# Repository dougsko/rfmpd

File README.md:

# RFMP Daemon

RF Microblog Protocol (RFMP) v0.5 daemon for packet radio networks.

## Overview

RFMP is a decentralized, append-only microblogging protocol for AX.25 UI frame packet radio networks. This daemon provides:

- Full RFMP protocol (Protocol Buffers wire format)
- Scuttlebutt-style vector clock synchronization
- REST API and real-time WebSocket updates
- Integrated web UI on port 8080
- SQLite persistent storage (pure Go, no CGo)
- Automatic Direwolf integration via udev
- Single static binary (~15MB), cross-compiles to ARM
- Native packages: `.deb`, `.rpm`, `.apk`, plus tarball

## Prerequisites

- [Go 1.24+](https://go.dev/dl/) (build only)
- Linux (Debian-based) for deployment
- [Direwolf](https://github.com/wb2osz/direwolf) TNC
- Amateur radio license (for transmission)
- Supported radio interface: Digirig, Digirig Lite, or QRP Labs QMX

## Building

```bash
# Build for current platform (stripped, version info baked in)
make build

# Plain build for current platform
go build -o rfmpd .

# Cross-compile for Raspberry Pi (ARM64)
GOOS=linux GOARCH=arm64 go build -o rfmpd .

# Cross-compile for Raspberry Pi (ARMv7) / Orange Pi Zero
GOOS=linux GOARCH=arm GOARM=7 go build -o rfmpd .

# Build all native packages (.deb, .rpm, .apk) for arm64 + amd64 (requires Docker)
make dist
```

`make build` uses `-ldflags "-s -w -X main.version=…"` to strip debug symbols
(reducing binary size ~30%) and embed the version string from the Makefile.

No CGo is required — the SQLite driver (`modernc.org/sqlite`) is pure Go, so cross-compilation works without a C toolchain.

## Running Tests

```bash
# Run unit tests
go test ./...

# Run protocol simulation (end-to-end)
go build -o rfmpd . && go build -o rf-sim ./cmd/rf-sim/
./rf-sim                        # All scenarios, unlimited speed
./rf-sim --baud 1200            # Simulate 1200 baud VHF channel
./rf-sim --baud 300             # Simulate 300 baud HF channel
./rf-sim --verbose              # Show broker frame traffic
./rf-sim --continuous           # Continuous churn testing
```

The simulation spawns multiple rfmpd nodes connected through an in-process
KISS broker, then verifies message delivery under various conditions:
network partitions, node crashes, late joiners, and fragmentation.

## Quick Start

```bash
# Build for current platform
make build

# Run in offline mode (no Direwolf needed)
./rfmpd -c config.yaml.example

# Run with verbose logging
./rfmpd -c config.yaml.example -v

# Open the web UI
open http://localhost:8080
```

## Installation (Linux)

Install from a native package — the `.deb`, `.rpm`, and `.apk` packages bundle
the binary, default config, systemd/OpenRC unit files, Direwolf configs, and
udev rules. Build them with `make dist` (requires Docker):

```bash
make dist             # builds .deb, .rpm, .apk, and tarballs in ./dist/

# Debian/Ubuntu/Raspberry Pi OS
sudo apt install ./dist/rfmpd_*_arm64.deb

# Fedora/RHEL
sudo dnf install ./dist/rfmpd-*.aarch64.rpm

# Alpine
sudo apk add --allow-untrusted ./dist/rfmpd-*-aarch64.apk
```

After install, set your callsign and start the service:

```bash
sudo nano /etc/rfmpd/config.yaml                       # set callsign
sudo nano /etc/rfmpd/direwolf/direwolf-digirig.conf    # set MYCALL to match
sudo systemctl enable --now rfmpd
```

Direwolf starts automatically when a supported radio interface is plugged in
via USB. For systems without package support, see
[packaging/INSTALL.md](packaging/INSTALL.md) for the manual tarball flow.
See [DEPLOYMENT.md](DEPLOYMENT.md) for full details on the hardware lifecycle.

## Uninstalling

```bash
# Debian/Ubuntu — keep config and data
sudo apt remove rfmpd
# Debian/Ubuntu — remove everything including config
sudo apt purge rfmpd

# Fedora/RHEL
sudo dnf remove rfmpd

# Alpine
sudo apk del rfmpd
```

## Supported Hardware

| Interface | Band | Baud | PTT | USB ID |
|-----------|------|------|-----|--------|
| Digirig | VHF | 1200 | Serial RTS | `10c4:ea60` |
| Digirig Lite | VHF | 1200 | CM108 GPIO | `0d8c:0012` (hidraw) |
| QMX | HF | 300 | Hamlib CAT | `0483:a34c` |

The packages install udev rules that auto-detect these devices and start Direwolf with the correct configuration.

## Configuration

Config file: `/etc/rfmpd/config.yaml` (installed) or `./config.yaml` (dev)

```yaml
node:
  callsign: "N0CALL"    # Your callsign (REQUIRED)
  ssid: 0               # SSID 0-15

network:
  direwolf_host: "127.0.0.1"
  direwolf_port: 8001
  offline_mode: false    # true for testing without radio

sync:
  sync_interval: 60     # SVEC broadcast interval (seconds)

storage:
  database_path: "/var/lib/rfmpd/messages.db"

api:
  host: "0.0.0.0"
  port: 8080
  cors_origins:
    - "http://localhost:8080"
```

## API

The daemon serves a REST API on port 8080 (configurable):

| Endpoint | Method | Description |
|----------|--------|-------------|
| `/` | GET | Web UI |
| `/health` | GET | Health check |
| `/messages` | GET | List messages (filterable) |
| `/messages/{id}` | GET | Get specific message |
| `/messages` | POST | Send a message |
| `/channels` | GET | List active channels |
| `/nodes` | GET | List seen nodes |
| `/status` | GET | Daemon status and vector clock |
| `/config/callsign` | GET/POST | Get or set callsign |
| `/stream` | WS | Real-time WebSocket updates |

```bash
# Send a message
curl -X POST http://localhost:8080/messages \
  -H "Content-Type: application/json" \
  -d '{"channel": "general", "body": "Hello RFMP!"}'

# Get recent messages
curl http://localhost:8080/messages?channel=general&limit=10

# Check status
curl http://localhost:8080/status
```

See [openapi.yaml](openapi.yaml) for the full API specification.

## Protocol

RFMP v0.4 uses Protocol Buffers for the RF wire format:

- **MSG** — Message with per-node monotonic sequence number, epoch timestamp, binary ID
- **FRAG** — Fragment for messages exceeding threshold (raw protobuf bytes, no base64)
- **SVEC** — Vector clock broadcast for scuttlebutt synchronization (native map type)

Protobuf encoding saves 30-50% airtime versus the previous text format. Synchronization uses per-node sequence numbers. Nodes broadcast their vector clock via SVEC frames; on receiving a remote SVEC, the local node pushes any messages the remote is missing.

See [docs/PROTOCOL.md](docs/PROTOCOL.md) for the complete protocol specification and [test_vectors.json](test_vectors.json) for conformance vectors.

## Display Simulator

A standalone pager-style UI that renders to a 240×320 framebuffer in the browser. Targets the hardware pager build (ILI9341 display + BBQ20KBD keyboard on Orange Pi Zero 2W) but develops entirely on desktop via a web-based canvas simulator — no SDL or native GUI library required.

```bash
# Build the display simulator
go build -tags sim -o rfmp-display-sim ./cmd/rfmp-display

# Run (point at your running rfmpd instance)
./rfmp-display-sim -addr http://localhost:8080

# Open the simulator canvas in your browser
open http://localhost:9090
```

The simulator serves a web page at `localhost:9090` with a pixel-accurate 240×320 canvas (scaled 2× to 480×640). Click the canvas to focus, then interact with the keyboard:

| Key | Action |
|-----|--------|
| Arrow Up/Down | Navigate lists, scroll messages |
| Enter | Select channel, send message |
| Escape | Go back |
| Any letter | Open compose screen |
| `n` | Create new channel (from channel list) |
| `d` | Delete empty channel (from channel list) |
| Backspace | Delete character in compose |

The display connects to rfmpd via the same REST API and WebSocket as the web UI. Messages sent from either interface appear in both in real-time.

```bash
# Cross-compile for hardware (Orange Pi Zero 2W)
GOOS=linux GOARCH=arm64 go build -tags hw -o rfmp-display ./cmd/rfmp-display
```

See [hardware/pager-concept.md](hardware/pager-concept.md) for the full hardware build plan and [hardware/carrier-hat/](hardware/carrier-hat/) for the carrier PCB design.

## Project Structure

```
rfmp-go/
├── main.go                    # Entry point, embed web UI, signal handling
├── config.yaml.example        # Example configuration
├── Makefile                   # Build + multi-arch package builds (Docker)
├── Dockerfile                 # Multi-stage build for .deb/.rpm/.apk/tarball
├── cmd/
│   ├── rf-sim/                # Protocol simulation test harness
│   │   ├── main.go            # CLI, scenario runner
│   │   ├── broker.go          # KISS broker with partition/baud simulation
│   │   ├── node.go            # Node subprocess lifecycle
│   │   ├── api.go             # HTTP client helpers
│   │   ├── wsclient.go        # WebSocket client for assertions
│   │   ├── scenarios.go       # Test scenarios
│   │   └── report.go          # Results output
│   └── rfmp-display/          # Pager display UI + simulator
│       ├── main.go            # Main loop, signal handling
│       ├── api.go             # HTTP client for rfmpd
│       ├── ws.go              # WebSocket client with reconnect
│       ├── backend.go         # Display/Keyboard/LED interfaces
│       ├── backend_sim.go     # Web-based canvas simulator (build tag: sim)
│       ├── backend_hw.go      # Hardware stubs (build tag: hw)
│       ├── sim.html           # Browser canvas renderer
│       ├── framebuffer.go     # RGB565 pixel buffer + drawing primitives
│       ├── font.go            # Embedded 8×16 VGA bitmap font
│       ├── colors.go          # RGB565 color constants
│       ├── ui.go              # Screen state machine
│       ├── ui_channels.go     # Channel list screen
│       ├── ui_timeline.go     # Message timeline screen
│       ├── ui_compose.go      # Text compose screen
│       └── ui_create_channel.go # Channel name input screen
├── internal/
│   ├── config/                # YAML config loading with defaults
│   ├── protocol/              # Protobuf wire format, frames, fragmentation, message IDs
│   │   └── pb/                # Generated protobuf code (.proto schema)
│   ├── network/               # KISS framing, AX.25, Direwolf TCP client
│   ├── storage/               # SQLite database (pure Go)
│   ├── sync/                  # Adaptive transmission timing
│   ├── api/                   # HTTP server, WebSocket, route handlers
│   └── daemon/                # Main orchestrator (loops, routing, sync)
├── web/                       # Embedded web UI (HTML/CSS/JS)
├── radio/                     # Direwolf configs and udev rules
├── packaging/                 # Per-format package metadata (deb/rpm/apk/systemd/openrc/mdev) + INSTALL.md
├── hardware/                  # Pager hardware: concept, carrier HAT, 3D-printable enclosure
├── docs/                      # Protocol specification + RFC
├── test_vectors.json          # Protocol conformance test vectors
└── DEPLOYMENT.md              # Deployment and hardware lifecycle docs
```

## License

MIT License

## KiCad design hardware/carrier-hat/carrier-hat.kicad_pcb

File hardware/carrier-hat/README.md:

# RFMP Pager Carrier HAT

A small PCB that plugs onto the Orange Pi Zero 2W 40-pin header and breaks out
all peripheral connections to two JST-XH connectors. Eliminates loose Dupont
wires and makes assembly plug-and-play.

## Board Specs

- **Dimensions:** 65 × 30 mm (matches OPi Zero 2W outline)
- **Layers:** 2 (F.Cu + B.Cu)
- **Connector type:** JST-XH (2.5mm pitch, locking, through-hole)
- **Mounting:** 4× M2.5 holes matching OPi standoff positions

## Schematic

```
                        RFMP Pager Carrier HAT
    ┌─────────────────────────────────────────────────────────┐
    │                                                         │
    │   ┌─────────────────────────┐    ┌──────────────────┐  │
    │   │  J1: 2×20 Female Header │    │ J2: DISPLAY      │  │
    │   │  (plugs onto OPi)       │    │ 8-pin JST-XH     │  │
    │   │                         │    │                   │  │
    │   │  Pin 1  ─── 3V3 bus ────┼────┤─ 1: 3V3          │  │
    │   │  Pin 6  ─── GND bus ────┼────┤─ 2: GND          │  │
    │   │  Pin 23 ─── SPI0_SCLK ─┼────┤─ 3: SCLK         │  │
    │   │  Pin 19 ─── SPI0_MOSI ─┼────┤─ 4: MOSI         │  │
    │   │  Pin 24 ─── SPI0_CE0 ──┼────┤─ 5: CS           │  │
    │   │  Pin 18 ─── GPIO24 ────┼────┤─ 6: DC           │  │
    │   │  Pin 12 ─── GPIO18 ────┼────┤─ 7: RST          │  │
    │   │  Pin 17 ─── 3V3 ───────┼────┤─ 8: BLK          │  │
    │   │                         │    └──────────────────┘  │
    │   │                         │    ┌──────────────────┐  │
    │   │                         │    │ J3: KEYBOARD     │  │
    │   │                         │    │ 5-pin JST-XH     │  │
    │   │                         │    │                   │  │
    │   │  Pin 1  ─── 3V3 bus ────┼────┤─ 1: 3V3          │  │
    │   │  Pin 9  ─── GND bus ────┼────┤─ 2: GND          │  │
    │   │  Pin 3  ─── I2C1_SDA ──┼────┤─ 3: SDA          │  │
    │   │  Pin 5  ─── I2C1_SCL ──┼────┤─ 4: SCL          │  │
    │   │  Pin 7  ─── GPIO4 ─────┼────┤─ 5: INT          │  │
    │   │                         │    └──────────────────┘  │
    │   └─────────────────────────┘                          │
    │                                                         │
    │   ┌──────────────────┐                                  │
    │   │ J4: SHUTDOWN BTN │                                  │
    │   │ 2-pin JST-XH    │                                  │
    │   │                  │                                  │
    │   │  Pin 11 ── PH2 ─┤─ 1: GPIO_SHUTDOWN               │
    │   │  GND ────────────┤─ 2: GND                         │
    │   └──────────────────┘                                  │
    │                                                         │
    │   [D1]──[R1 220Ω]──── Pin 29 (GPIO5)    Status LED    │
    │     │                                                   │
    │     └── GND (Pin 30)                                    │
    │                                                         │
    │   [C1 100nF] across 3V3/GND    Decoupling              │
    │                                                         │
    └─────────────────────────────────────────────────────────┘
```

## Pin Mapping (OPi Header → JST Connectors)

| OPi Pin | Signal | H618 Pad | Routed To |
|---------|--------|----------|-----------|
| 1 | 3.3V | — | J2.1, J3.1 |
| 3 | I2C1_SDA | PI8 | J3.3 |
| 5 | I2C1_SCL | PI7 | J3.4 |
| 6 | GND | — | J2.2 |
| 7 | GPIO4 | PI13 | J3.5 (KB INT) |
| 9 | GND | — | J3.2 |
| 11 | GPIO17 | PH2 | J4.1 (Shutdown BTN) |
| 12 | GPIO18 | PI1 | J2.7 (DSP RST) |
| 17 | 3.3V | — | J2.8 (BLK, via 3V3 bus) |
| 18 | GPIO24 | PH4 | J2.6 (DSP DC) |
| 19 | SPI0_MOSI | PH7 | J2.4 |
| 23 | SPI0_SCLK | PH6 | J2.3 |
| 24 | SPI0_CE0 | PH5 | J2.5 |
| 29 | GPIO5 | PI0 | R1 → D1 (LED) |
| 30 | GND | — | D1 cathode |

## Bill of Materials (HAT only)

| Ref | Part | Package | Qty | Notes |
|-----|------|---------|-----|-------|
| J1 | 2×20 female header, 2.54mm | Through-hole | 1 | Plugs onto OPi |
| J2 | JST-XH 8-pin right-angle | B8B-XH-A | 1 | Display |
| J3 | JST-XH 5-pin right-angle | B5B-XH-A | 1 | Keyboard |
| J4 | JST-XH 2-pin right-angle | B2B-XH-A | 1 | Shutdown button |
| R1 | 220Ω resistor | 0805 or axial | 1 | LED current limit |
| D1 | LED 3mm green | Through-hole | 1 | Status indicator |
| C1 | 100nF ceramic | 0805 | 1 | 3V3 decoupling |

## Fabrication

Order from JLCPCB or PCBWay:
- Upload the Gerber files (export from KiCad: File → Fabrication Outputs → Gerbers)
- Settings: 2-layer, 1.6mm thickness, HASL finish, any color
- Minimum order: 5 boards, ~$5 total + shipping
- Turnaround: 3-5 days fabrication + 5-10 days shipping

## Assembly Notes

### Soldering the HAT

1. Solder J1 (2×20 female header) on the **bottom** of the board — this plugs
   down onto the OPi's male header pins
2. Solder J2, J3 (JST-XH connectors) on the **top**, angled toward the
   board edge for easy cable access
3. Solder R1, D1, C1 on the top side

### Connecting Peripherals

The easiest connection method for each peripheral:

| Peripheral | Connection Method | What to Buy |
|------------|-------------------|-------------|
| ILI9341 display | Solder JST-XH 8-pin pigtail into display header holes | "JST-XH 8-pin pigtail 10cm" |
| BBQ20KBD keyboard | Qwiic cable (4-pin) for I2C+power, plus 1 wire for INT | "Qwiic cable 10cm" + 1× Dupont F-F |
| Shutdown button | JST-XH 2-pin pigtail to a momentary tactile switch | "JST-XH 2-pin pigtail" + tactile button |
| Status LED | Mounted directly on HAT (D1) | Included on board |

**Detailed steps:**

#### Display (ILI9341)

The display module has 8 through-hole pin positions. Most ship with a
pre-soldered male header — desolder it (or buy the module without header):

1. Get a JST-XH 8-pin pigtail (plug on one end, bare tinned wires on the other)
2. Thread the 8 bare wires through the display's header holes from the back
3. Solder on the front side, trim excess
4. The JST plug end connects to J2 on the HAT

Pin order on the pigtail must match J2: `3V3, GND, SCLK, MOSI, CS, DC, RST, BLK`

Most ILI9341 modules label their pins left-to-right as:
`VCC, GND, CS, RESET, DC, SDI(MOSI), SCK, LED`

So the pigtail wire mapping is:

| Pigtail Wire (J2 pin) | Display Module Pin |
|------------------------|--------------------|
| 1 (3V3) | VCC |
| 2 (GND) | GND |
| 3 (SCLK) | SCK |
| 4 (MOSI) | SDI/MOSI |
| 5 (CS) | CS |
| 6 (DC) | DC |
| 7 (RST) | RESET |
| 8 (BLK) | LED |

Note: module pin order varies by manufacturer — verify your specific module's
silkscreen before soldering. If the order doesn't match, just arrange the
pigtail wires accordingly.

#### Keyboard (BBQ20KBD)

The BBQ20KBD already has a Qwiic/STEMMA QT connector (JST-SH 4-pin, 1mm pitch)
providing I2C + power. Only the INT pin needs a manual wire:

1. Buy a pre-made Qwiic cable (4-pin JST-SH, 10cm)
2. Cut one end off the Qwiic cable, strip the 4 wires
3. Solder those 4 wires to a JST-XH 5-pin pigtail on positions 1-4:
   - Red → pin 1 (3V3)
   - Black → pin 2 (GND)
   - Blue → pin 3 (SDA)
   - Yellow → pin 4 (SCL)
4. For pin 5 (INT): solder a single wire from the BBQ20KBD INT pad to
   position 5 on the same JST-XH pigtail
5. Plug the JST-XH end into J3 on the HAT

Alternative: skip the Qwiic cable entirely and solder a 5-pin JST-XH pigtail
directly to the BBQ20KBD's through-hole pads (3V3, GND, SDA, SCL, INT are all
available as solder points on the board).

#### Shutdown Button

A momentary tactile switch connected to J4 triggers a clean OS shutdown
(prevents SD card corruption from pulling power):

1. Get a JST-XH 2-pin pigtail (plug on one end, bare wires on the other)
2. Solder the two bare wires to the two NO (normally-open) terminals of a
   momentary tactile push button
3. Plug the JST end into J4 on the HAT

Pin 1 is GPIO_SHUTDOWN (pulled high internally); pin 2 is GND. Pressing the
button pulls the GPIO low, which the software debounces and then calls
`shutdown -h now`.

### Physical Assembly in Enclosure

```
┌─────────── Enclosure Lid ───────────────┐
│                                         │
│  ┌───────────────────────────────────┐  │
│  │         ILI9341 Display           │  │  ← Mounted with M2 screws
│  └────────────────┬──────────────────┘  │    through module corner holes
│                   │ JST cable (~8cm)    │
│  ┌────────────────┼─────────────────┐   │
│  │   BBQ20KBD Keyboard              │   │  ← KB screwed down
│  │   [Q][W][E][R][T][Y]...          │   │
│  │         [trackpad]               │   │
│  └────────────────┼─────────────────┘   │
│                   │                     │
└───────────────────┼─────────────────────┘
                    │
    JST cables run  │  (~8cm each)
    through gap     │
                    │
┌───────────────────┼─────────────────────┐
│                   │                     │
│  ┌────────────────┴──────────────────┐  │
│  │       Carrier HAT                 │  │
│  │  [J2]  [J3]  ←── cables          │  │  ← JST plugs click in here
│  │       [D1 LED]                    │  │
│  │  ═══════════════════════════════  │  │
│  │  ║  2×20 female header (bottom) ║  │  │
│  └──╨════════════════════════════╨──┘  │
│     ║   Orange Pi Zero 2W        ║     │
│     ║   [USB-C]  [40-pin header] ║     │  ← OPi screwed to bottom
│     ╚════════════════════════════╝     │    standoffs; HAT plugs on top
│                                         │
│  [IP5306 power module]  [LiPo]          │  ← Tucked beside OPi
│                                         │
└─────────── Enclosure Bottom ────────────┘
```

Total solder joints: ~15 (8 display + 5 keyboard + HAT components)
Total cables: 2 JST-XH (click in, click out)

## Shopping List (cables & connectors)

| Item | Qty | Search Term (AliExpress/Amazon) | ~Price |
|------|-----|--------------------------------|--------|
| JST-XH 8-pin pigtail, 10cm | 1 | "JST XH 2.54 8pin wire 10cm" | $0.50 |
| JST-XH 5-pin pigtail, 10cm | 1 | "JST XH 2.54 5pin wire 10cm" | $0.50 |
| JST-XH 2-pin pigtail, 10cm | 1 | "JST XH 2.54 2pin wire 10cm" | $0.30 |
| Tactile push button (momentary, NO) | 1 | "6x6mm tactile push button" | $0.10 |
| Qwiic cable 10cm (optional, for KB) | 1 | "Qwiic STEMMA QT cable 100mm" | $1.50 |

Or buy a JST-XH pigtail assortment pack (~$5 for 20 pieces in various pin counts).

## Project Files

```
hardware/carrier-hat/
├── README.md                # This file — design spec and assembly guide
├── carrier-hat.kicad_pro    # KiCad project
├── carrier-hat.kicad_sch    # KiCad schematic
└── carrier-hat.kicad_pcb    # KiCad PCB outline + placement
```

Open `carrier-hat.kicad_pro` in KiCad 8+. The schematic defines all components
and connectivity. The PCB file has the board outline and mounting holes —
footprints need final placement and trace routing in the interactive router.
Export Gerbers and upload to JLCPCB/PCBWay.

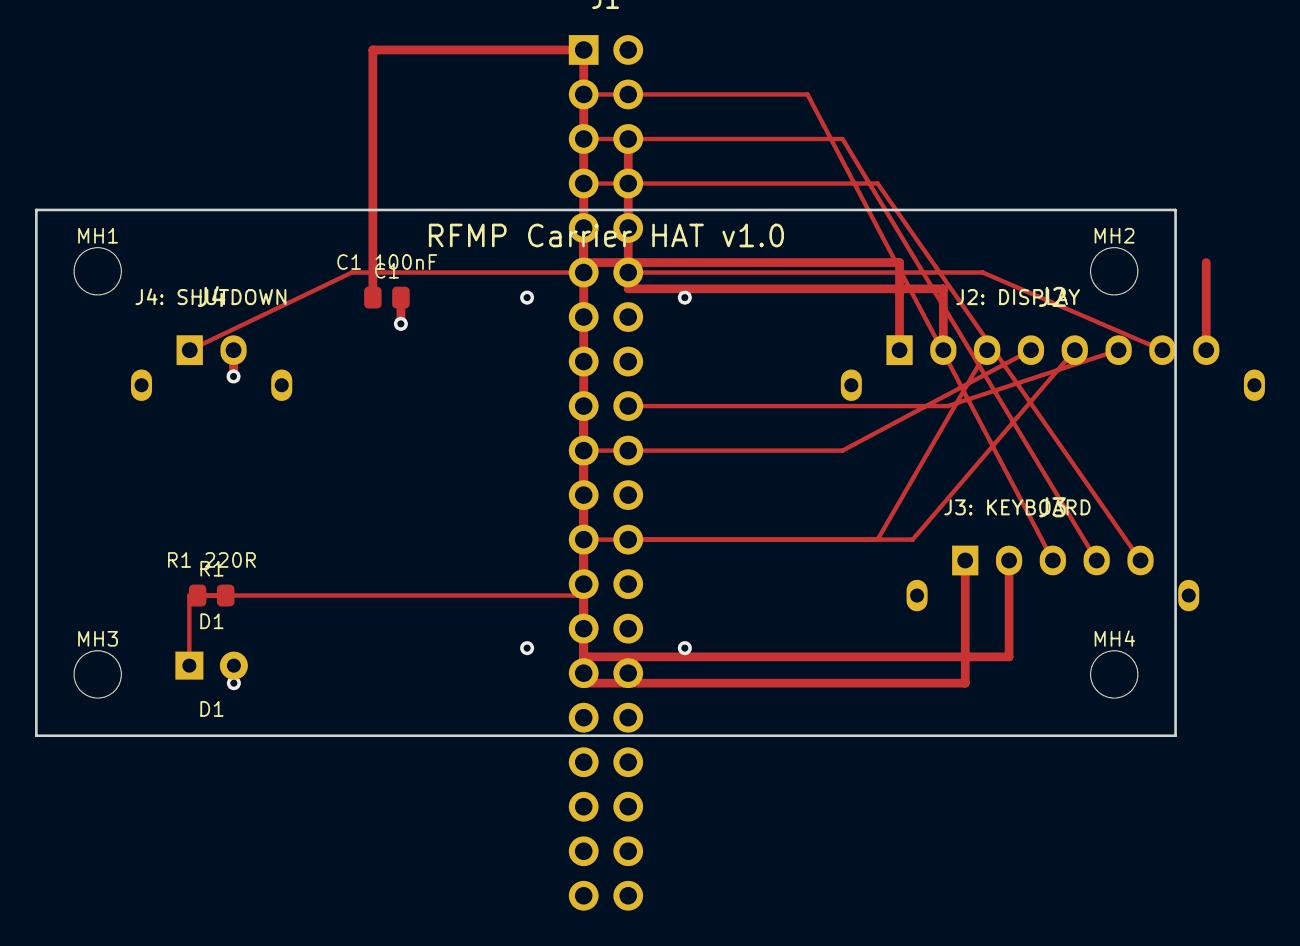
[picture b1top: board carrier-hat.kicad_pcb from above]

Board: 2 copper layers, 65.0 x 30.0 mm, 11 parts (0 on the bottom side), 12 nets.

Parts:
C1: 100nF; R_0805_2012Metric
D1: LED_3mm; LED_D3.0mm
J1: PinHeader_2x20; PinHeader_2x20_P2.54mm_Vertical
J2: JST_XH_8pin; JST_XH_B8B-XH-A_1x08_P2.50mm_Horizontal
J3: JST_XH_5pin; JST_XH_B5B-XH-A_1x05_P2.50mm_Horizontal
J4: JST_XH_2pin; JST_XH_B2B-XH-A_1x02_P2.50mm_Horizontal
MH1, MH2, MH3, MH4: MountingHole; MountingHole_2.7mm_M2.5
R1: 220R; R_0805_2012Metric

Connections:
3V3: C1.1, J1.1, J1.17, J2.1, J2.8, J3.1
GND: C1.2, D1.2, J1.6, J1.9, J1.30, J2.2, J3.2, J4.2
GPIO_DC: J1.18, J2.6
GPIO_INT: J1.7, J3.5
GPIO_LED: D1.1, J1.29, R1.1, R1.2
GPIO_RST: J1.12, J2.7
GPIO_SHUTDOWN: J1.11, J4.1
I2C1_SCL: J1.5, J3.4
I2C1_SDA: J1.3, J3.3
SPI0_CE0: J1.24, J2.5
SPI0_MOSI: J1.19, J2.4
SPI0_SCLK: J1.23, J2.3

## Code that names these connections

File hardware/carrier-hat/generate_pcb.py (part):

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    (5, "SPI0_CE0"),
    (6, "I2C1_SDA"),
    (7, "I2C1_SCL"),
    (8, "GPIO_DC"),
    (9, "GPIO_RST"),
    (10, "GPIO_INT"),
    (11, "GPIO_LED"),
    (12, "GPIO_SHUTDOWN"),
]

NET_BY_NAME = {name: idx for idx, name in NETS if name}
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    6: "GND", 9: "GND", 30: "GND",
    19: "SPI0_MOSI", 23: "SPI0_SCLK", 24: "SPI0_CE0",
    3: "I2C1_SDA", 5: "I2C1_SCL",
    18: "GPIO_DC", 12: "GPIO_RST", 7: "GPIO_INT",
    29: "GPIO_LED",
    11: "GPIO_SHUTDOWN",
}

J2_PIN_NETS = {
    1: "3V3", 2: "GND", 3: "SPI0_SCLK", 4: "SPI0_MOSI",
    5: "SPI0_CE0", 6: "GPIO_DC", 7: "GPIO_RST", 8: "3V3",
}

J3_PIN_NETS = {
    1: "3V3", 2: "GND", 3: "I2C1_SDA", 4: "I2C1_SCL", 5: "GPIO_INT",
}

J4_PIN_NETS = {1: "GPIO_SHUTDOWN", 2: "GND"}


def uid():
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
    # --- Display signals: J1 → J2 ---

    # SPI0_SCLK: J1 pin 23 → J2 pin 3
    x1, y1 = J1_PADS[23]
    x2, y2 = J2_PADS[3]
    mid_x = 48.0
    t(x1, y1, mid_x, y1, TRACE_SIGNAL, "SPI0_SCLK")
    t(mid_x, y1, x2, y2, TRACE_SIGNAL, "SPI0_SCLK")

    # SPI0_MOSI: J1 pin 19 → J2 pin 4
    x1, y1 = J1_PADS[19]
    x2, y2 = J2_PADS[4]
    mid_x = 46.0
    t(x1, y1, mid_x, y1, TRACE_SIGNAL, "SPI0_MOSI")
    t(mid_x, y1, x2, y2, TRACE_SIGNAL, "SPI0_MOSI")

    # SPI0_CE0: J1 pin 24 → J2 pin 5
    x1, y1 = J1_PADS[24]
    x2, y2 = J2_PADS[5]
    mid_x = 50.0
    t(x1, y1, mid_x, y1, TRACE_SIGNAL, "SPI0_CE0")
    t(mid_x, y1, x2, y2, TRACE_SIGNAL, "SPI0_CE0")

    # GPIO_DC: J1 pin 18 → J2 pin 6
    x1, y1 = J1_PADS[18]
    x2, y2 = J2_PADS[6]
    mid_x = 52.0
    t(x1, y1, mid_x, y1, TRACE_SIGNAL, "GPIO_DC")
    t(mid_x, y1, x2, y2, TRACE_SIGNAL, "GPIO_DC")

    # GPIO_RST: J1 pin 12 → J2 pin 7
    x1, y1 = J1_PADS[12]
    x2, y2 = J2_PADS[7]
    mid_x = 54.0
    t(x1, y1, mid_x, y1, TRACE_SIGNAL, "GPIO_RST")
    t(mid_x, y1, x2, y2, TRACE_SIGNAL, "GPIO_RST")

    # --- Keyboard signals: J1 → J3 ---

    # I2C1_SDA: J1 pin 3 → J3 pin 3
    x1, y1 = J1_PADS[3]
    x2, y2 = J3_PADS[3]
    mid_x = 44.0
    t(x1, y1, mid_x, y1, TRACE_SIGNAL, "I2C1_SDA")
    t(mid_x, y1, x2, y2, TRACE_SIGNAL, "I2C1_SDA")

    # I2C1_SCL: J1 pin 5 → J3 pin 4
    x1, y1 = J1_PADS[5]
    x2, y2 = J3_PADS[4]
    mid_x = 46.0
    t(x1, y1, mid_x, y1, TRACE_SIGNAL, "I2C1_SCL")
    t(mid_x, y1, x2, y2, TRACE_SIGNAL, "I2C1_SCL")

    # GPIO_INT: J1 pin 7 → J3 pin 5
    x1, y1 = J1_PADS[7]
    x2, y2 = J3_PADS[5]
    mid_x = 48.0
    t(x1, y1, mid_x, y1, TRACE_SIGNAL, "GPIO_INT")
    t(mid_x, y1, x2, y2, TRACE_SIGNAL, "GPIO_INT")

    # --- Power: 3V3 ---

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    # J1 pin 29 → R1 pad 1
    x1, y1 = J1_PADS[29]
    x2, y2 = R1_PADS[1]
    t(x1, y1, x1, y2, TRACE_SIGNAL, "GPIO_LED")
    t(x1, y2, x2, y2, TRACE_SIGNAL, "GPIO_LED")

    # R1 pad 2 → D1 pad 1 (anode)
    x1, y1 = R1_PADS[2]
    x2, y2 = D1_PADS[1]
    t(x1, y1, x2, y1, TRACE_SIGNAL, "GPIO_LED")
    t(x2, y1, x2, y2, TRACE_SIGNAL, "GPIO_LED")

    # D1 pad 2 (cathode) → GND via
    x1, y1 = D1_PADS[2]
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
    # --- Shutdown button: J1 pin 11 → J4 ---

    # GPIO_SHUTDOWN: J1 pin 11 → J4 pin 1
    x1, y1 = J1_PADS[11]
    x2, y2 = J4_PADS[1]
    mid_x = 18.0
    t(x1, y1, mid_x, y1, TRACE_SIGNAL, "GPIO_SHUTDOWN")
    t(mid_x, y1, x2, y2, TRACE_SIGNAL, "GPIO_SHUTDOWN")

    # J4 pin 2 (GND) → via to ground pour
    x1, y1 = J4_PADS[2]
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        gen_jst_connector("J2", 8, *J2_POS, J2_PIN_NETS),
        gen_jst_connector("J3", 5, *J3_POS, J3_PIN_NETS),
        gen_jst_connector("J4", 2, *J4_POS, J4_PIN_NETS),
        gen_smd_0805("R1", "220R", *R1_POS, "GPIO_LED", "GPIO_LED"),
        gen_smd_0805("C1", "100nF", *C1_POS, "3V3", "GND"),
        gen_led_3mm("D1", *D1_POS, "GPIO_LED", "GND"),
        "",
        gen_traces(),
        "",
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
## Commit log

2026-05-22 dockerfile
2026-05-22 makefile
2026-05-23 version bump
2026-05-23 docker
2026-05-23 version
